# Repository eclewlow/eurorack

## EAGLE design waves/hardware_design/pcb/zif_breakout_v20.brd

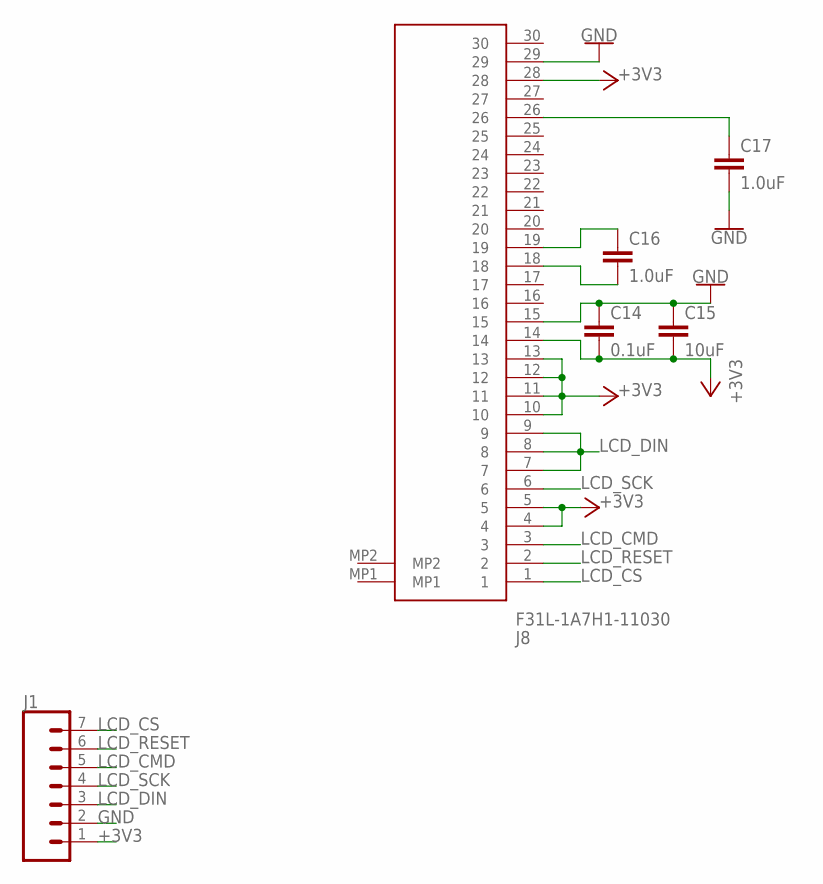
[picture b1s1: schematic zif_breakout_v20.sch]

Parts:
C14: 0.1uF; 0603
C15: 10uF; 0603
C16, C17: 1.0uF; 0603
J1: CONN_07; 1X07
J8: F31L-1A7H1-11030; F31L1A7H111030

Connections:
+3V3: C14.2, C15.2, J1.1, J8.4, J8.5, J8.10, J8.11, J8.12, J8.13, J8.14, J8.28
GND: C14.1, C15.1, C17.2, J1.2, J8.15, J8.29
LCD_CMD: J1.5, J8.3
LCD_CS: J1.7, J8.1
LCD_DIN: J1.3, J8.7, J8.8, J8.9
LCD_RESET: J1.6, J8.2
LCD_SCK: J1.4, J8.6
unnamed: C16.1, J8.19
unnamed: C17.1, J8.26
unnamed: C16.2, J8.18

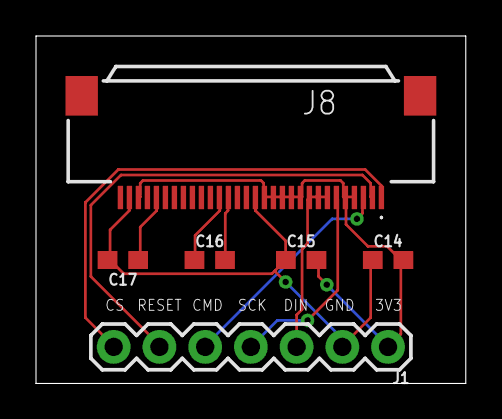
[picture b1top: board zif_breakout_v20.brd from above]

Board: 2 copper layers, 23.9 x 19.3 mm, 6 parts (0 on the bottom side), 10 nets.

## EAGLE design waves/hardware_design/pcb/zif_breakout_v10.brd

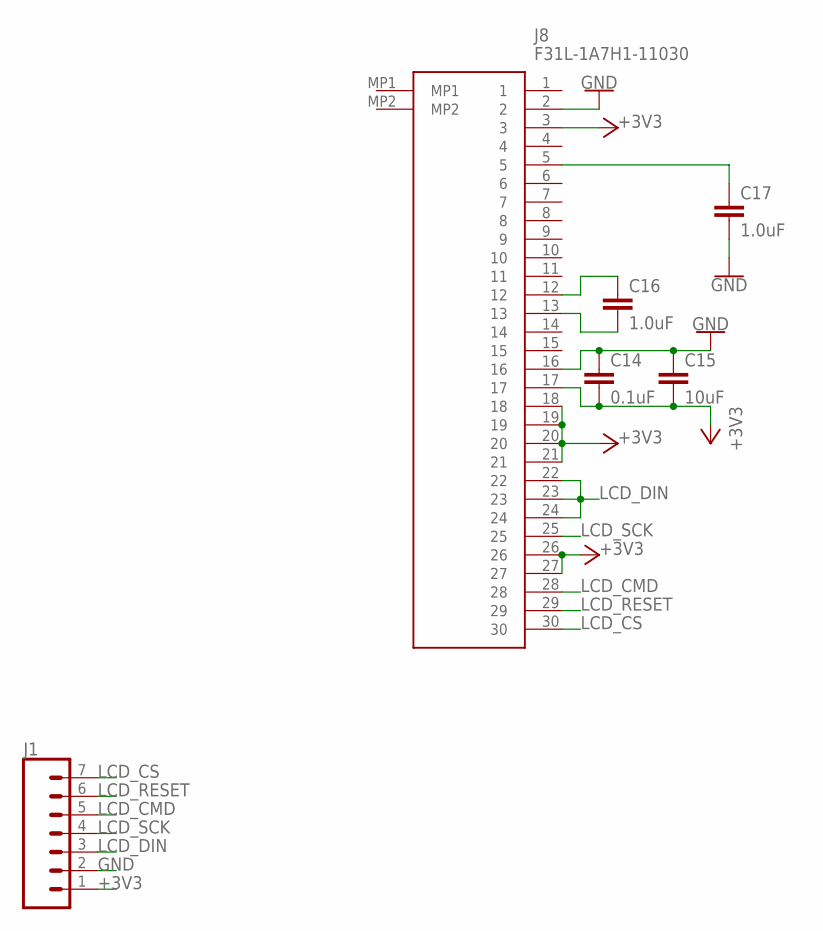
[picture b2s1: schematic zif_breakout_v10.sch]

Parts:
C14: 0.1uF; 0603
C15: 10uF; 0603
C16, C17: 1.0uF; 0603
J1: CONN_07; 1X07
J8: F31L-1A7H1-11030; F31L1A7H111030

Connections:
+3V3: C14.2, C15.2, J1.1, J8.3, J8.17, J8.18, J8.19, J8.20, J8.21, J8.26, J8.27
GND: C14.1, C15.1, C17.2, J1.2, J8.2, J8.16
LCD_CMD: J1.5, J8.28
LCD_CS: J1.7, J8.30
LCD_DIN: J1.3, J8.22, J8.23, J8.24
LCD_RESET: J1.6, J8.29
LCD_SCK: J1.4, J8.25
unnamed: C17.1, J8.5
unnamed: C16.2, J8.13
unnamed: C16.1, J8.12

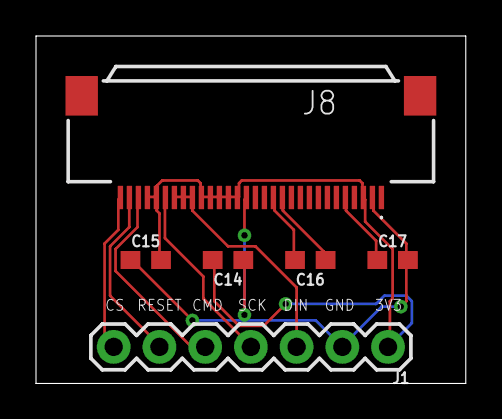
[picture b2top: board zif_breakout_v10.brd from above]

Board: 2 copper layers, 23.9 x 19.3 mm, 6 parts (0 on the bottom side), 10 nets.

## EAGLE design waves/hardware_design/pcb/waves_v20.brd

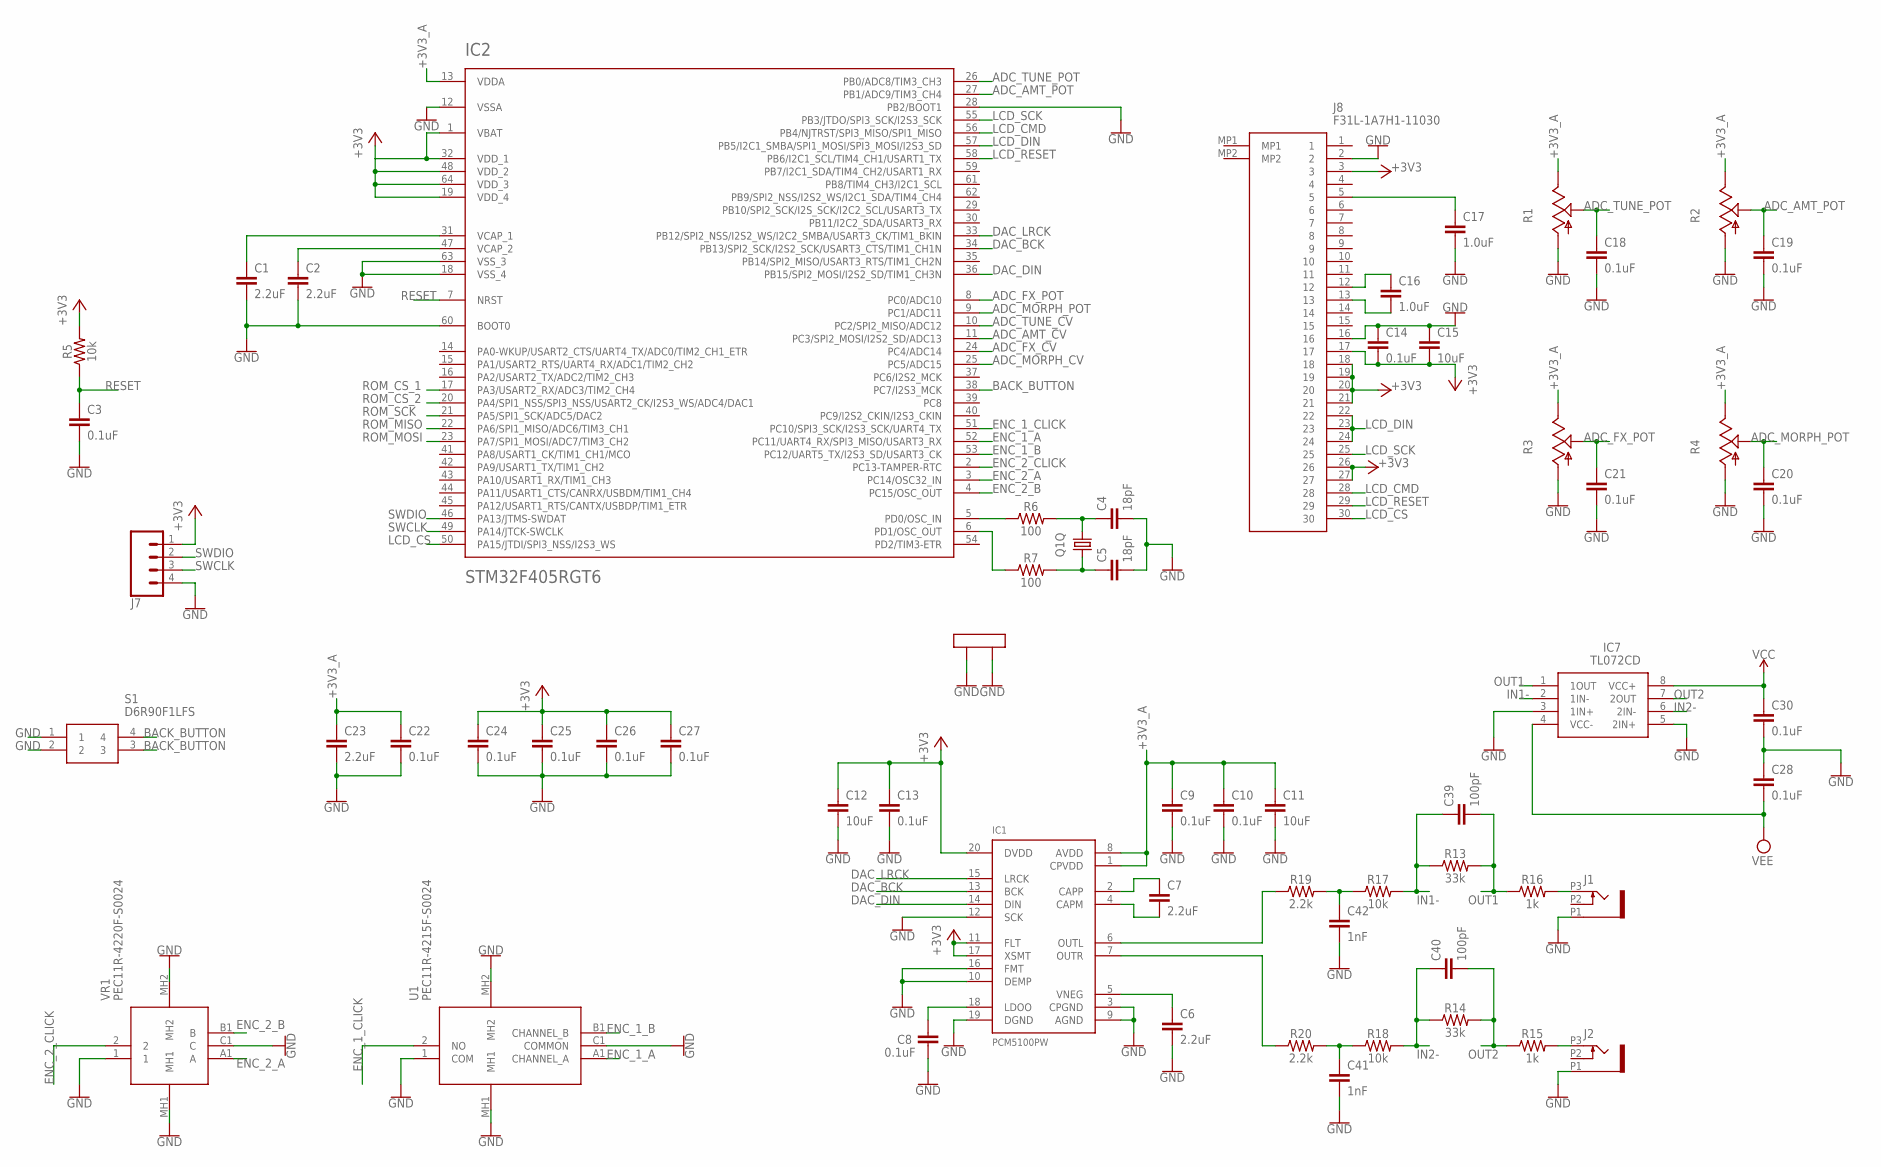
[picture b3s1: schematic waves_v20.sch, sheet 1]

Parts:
C1, C2, C6, C7, C23: 2.2uF; 0603
C3, C8, C9, C10, C13, C14, C18, C19, C20, C21, C22, C24, C25, C26, C27, C28, C30: 0.1uF; 0603
C4, C5: 18pF; 0603
C11, C12, C15: 10uF; 0603
C16, C17: 1.0uF; 0603
C39, C40: 100pF; 0603
C41, C42: 1nF; 0603
IC1: PCM5100PW; SSOP20
IC2: STM32F405RGT6; TQFP-10X10-64
IC7: TL072CD; SOIC127P600X175-8N
J1, J2: PJ301_THONKICONN6; WQP_PJ_301M6
J7: CONN_04; 1X04
J8: F31L-1A7H1-11030; F31L1A7H111030
Q1: CRYSTAL; CTS406
R1, R2, R3, R4: POT_USVERTICAL_PS; ALPS_POT_VERTICAL_PS
R5, R17, R18: 10k; 0603
R6, R7: 100; 0603
R13, R14: 33k; 0603
R15, R16: 1k; 0603
R19, R20: 2.2k; 0603
S1: D6R90F1LFS; D6C10F1LFS
U1: PEC11R-4215F-S0024; PEC11R4215FS0024
VR1: PEC11R-4220F-S0024; PEC11R4220FS0024

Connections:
+3V3: C12.1, C13.1, C14.2, C15.2, C24.1, C25.1, C26.1, C27.1, IC1.11 (FLT), IC1.17 (XSMT), IC1.20 (DVDD), IC2.1 (VBAT), IC2.19 (VDD_4), IC2.32 (VDD_1), IC2.48 (VDD_2), IC2.64 (VDD_3), J7.1, J8.3, J8.17, J8.18, J8.19, J8.20, J8.21, J8.26, J8.27, R5.2; also elsewhere on the board
+3V3_A: C9.1, C10.1, C11.1, C22.1, C23.1, IC1.1 (CPVDD), IC1.8 (AVDD), IC2.13 (VDDA), R1.P$1 (E), R2.P$1 (E), R3.P$1 (E), R4.P$1 (E); also elsewhere on the board
ADC_AMT_CV: IC2.11 (PC3/SPI2_MOSI/I2S2_SD/ADC13); also elsewhere on the board
ADC_AMT_POT: C19.1, IC2.27 (PB1/ADC9/TIM3_CH4), R2.P$2 (S)
ADC_FX_CV: IC2.24 (PC4/ADC14); also elsewhere on the board
ADC_FX_POT: C21.1, IC2.8 (PC0/ADC10), R3.P$2 (S)
ADC_MORPH_CV: IC2.25 (PC5/ADC15); also elsewhere on the board
ADC_MORPH_POT: C20.1, IC2.9 (PC1/ADC11), R4.P$2 (S)
ADC_TUNE_CV: IC2.10 (PC2/SPI2_MISO/ADC12); also elsewhere on the board
ADC_TUNE_POT: C18.1, IC2.26 (PB0/ADC8/TIM3_CH3), R1.P$2 (S)
BACK_BUTTON: IC2.38 (PC7/I2S3_MCK), S1.3, S1.4
DAC_BCK: IC1.13 (BCK), IC2.34 (PB13/SPI2_SCK/I2S2_SCK/USART3_CTS/TIM1_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)
DAC_DIN: IC1.14 (DIN), IC2.36 (PB15/SPI2_MOSI/I2S2_SD/TIM1_CH3N)
DAC_LRCK: IC1.15 (LRCK), IC2.33 (PB12/SPI2_NSS/I2S2_WS/I2C2_SMBA/USART3_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)
ENC_1_A: IC2.52 (PC11/UART4_RX/SPI3_MISO/USART3_RX), U1.A1 (CHANNEL_A)
ENC_1_B: IC2.53 (PC12/UART5_TX/I2S3_SD/USART3_CK), U1.B1 (CHANNEL_B)
ENC_1_CLICK: IC2.51 (PC10/SPI3_SCK/I2S3_SCK/UART4_TX), U1.2 (NO)
ENC_2_A: IC2.3 (PC14/OSC32_IN), VR1.A1 (A)
ENC_2_B: IC2.4 (PC15/OSC_OUT), VR1.B1 (B)
ENC_2_CLICK: IC2.2 (PC13-TAMPER-RTC), VR1.2
GND: C1.2, C2.2, C3.2, C4.2, C5.2, C6.2, C8.2, C9.2, C10.2, C11.2, C12.2, C13.2, C14.1, C15.1, C17.2, C18.2, C19.2, C20.2, C21.2, C22.2, C23.2, C24.2, C25.2, C26.2, C27.2, C28.1, C30.2, C41.2, C42.2, IC1.3 (CPGND), IC1.9 (AGND), IC1.10 (DEMP), IC1.12 (SCK), IC1.16 (FMT), IC1.19 (DGND), IC2.12 (VSSA), IC2.18 (VSS_4), IC2.28 (PB2/BOOT1), IC2.60 (BOOT0), IC2.63 (VSS_3), IC7.3 (1IN+), IC7.5 (2IN+), J1.P1 (1), J2.P1 (1), J7.4, J8.2, J8.16, Q1.2 (LID1), Q1.4 (LID2), R1.P$3 (A), R2.P$3 (A), R3.P$3 (A), R4.P$3 (A), S1.1, S1.2, U1.1 (COM), U1.C1 (COMMON), U1.MH1, U1.MH2, VR1.1, VR1.C1 (C), VR1.MH1, VR1.MH2; also elsewhere on the board
IN1-: C39.1, IC7.2 (1IN-), R13.1, R17.2
IN2-: C40.1, IC7.6 (2IN-), R14.1, R18.2
LCD_CMD: IC2.56 (PB4/NJTRST/SPI3_MISO/SPI1_MISO), J8.28
LCD_CS: IC2.50 (PA15/JTDI/SPI3_NSS/I2S3_WS), J8.30
LCD_DIN: IC2.57 (PB5/I2C1_SMBA/SPI1_MOSI/SPI3_MOSI/I2S3_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), J8.22, J8.23, J8.24
LCD_RESET: IC2.58 (PB6/I2C1_SCL/TIM4_CH1/USART1_TX), J8.29
LCD_SCK: IC2.55 (PB3/JTDO/SPI3_SCK/I2S3_SCK), J8.25
unnamed: C1.1, IC2.31 (VCAP_1)
unnamed: C2.1, IC2.47 (VCAP_2)
unnamed: C17.1, J8.5
unnamed: C6.1, IC1.5 (VNEG)
unnamed: C8.1, IC1.18 (LDOO)
unnamed: C7.1, IC1.2 (CAPP)
unnamed: C4.1, Q1.3 (2), R6.2
unnamed: IC2.6 (PD1/OSC_OUT), R7.1
unnamed: IC2.5 (PD0/OSC_IN), R6.1
unnamed: C5.1, Q1.1, R7.2
unnamed: C7.2, IC1.4 (CAPM)
unnamed: C16.2, J8.13
unnamed: C16.1, J8.12
unnamed: IC1.6 (OUTL), R19.1
unnamed: IC1.7 (OUTR), R20.1
unnamed: J2.P3 (3), R15.2
unnamed: J1.P3 (3), R16.2
unnamed: C42.1, R17.1, R19.2
unnamed: C41.1, R18.1, R20.2
OUT1: C39.2, IC7.1 (1OUT), R13.2, R16.1
OUT2: C40.2, IC7.7 (2OUT), R14.2, R15.1
RESET: C3.1, IC2.7 (NRST), R5.1
ROM_CS_1: IC2.17 (PA3/USART2_RX/ADC3/TIM2_CH4); also elsewhere on the board
ROM_CS_2: IC2.20 (PA4/SPI1_NSS/SPI3_NSS/USART2_CK/I2S3_WS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); also elsewhere on the board
ROM_MISO: IC2.22 (PA6/SPI1_MISO/ADC6/TIM3_CH1); also elsewhere on the board
ROM_MOSI: IC2.23 (PA7/SPI1_MOSI/ADC7/TIM3_CH2); also elsewhere on the board
ROM_SCK: IC2.21 (PA5/SPI1_SCK/ADC5/DAC2); also elsewhere on the board
SWCLK: IC2.49 (PA14/JTCK-SWCLK), J7.3
SWDIO: IC2.46 (PA13/JTMS-SWDAT), J7.2
VCC: C30.1, IC7.8 (VCC+); also elsewhere on the board
VEE: C28.2, IC7.4 (VCC-); also elsewhere on the board

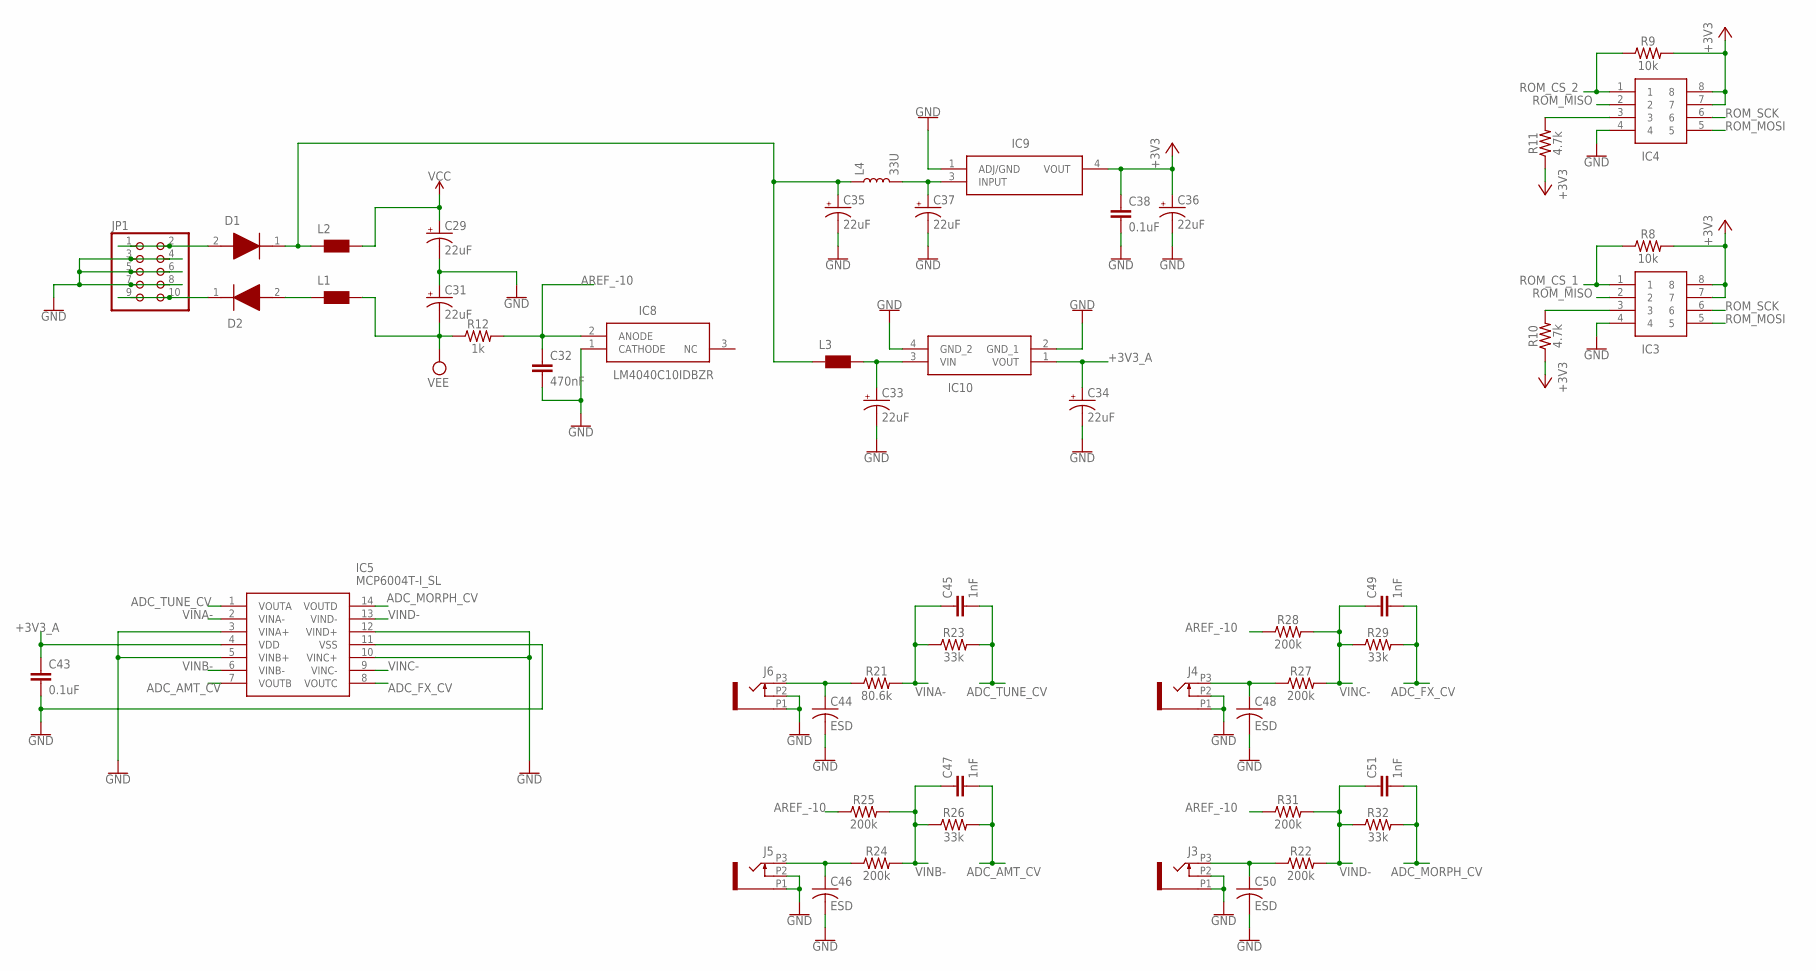
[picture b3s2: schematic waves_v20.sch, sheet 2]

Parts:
C29, C31, C33, C34, C35, C36, C37: 22uF; PANASONIC_C
C32: 470nF; 0402
C38, C43: 0.1uF; 0603
C44, C46, C48, C50: ESD; C0603
C45, C47, C49, C51: 1nF; 0603
D1, D2: 1N5819HW-7-F; SOD3716X145N
IC3, IC4: 1-2199298-2; DIPS762W70P254L1016H510Q8N
IC5: MCP6004T-I_SL; SOIC127P600X175-14N
IC8: LM4040C10IDBZR; SOT95P237X112-3N
IC9: LM1117DT-3.3_NOPB; TO228P991X238-3N
IC10: LD2981ABU33TR
J3, J4, J5, J6: PJ301_THONKICONN6; WQP_PJ_301M6
JP1: PINHD-2X5; 2X05
L1, L2, L3: WE-CBF_0603; 0603
L4: 33U; 0805
R8, R9: 10k; 0603
R10, R11: 4.7k; 0603
R12: 1k; 0603
R21: 80.6k; 0603
R22, R24, R25, R27, R28, R31: 200k; 0603
R23, R26, R29, R32: 33k; 0603

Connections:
+3V3: C36.+, C38.1, IC3.7, IC3.8, IC4.7, IC4.8, IC9.4 (VOUT), R8.2, R9.2, R10.1, R11.1; also elsewhere on the board
+3V3_A: C34.+, C43.1, IC5.4 (VDD), IC10.1 (VOUT); also elsewhere on the board
ADC_AMT_CV: C47.2, IC5.7 (VOUTB), R26.2; also elsewhere on the board
ADC_FX_CV: C49.2, IC5.8 (VOUTC), R29.2; also elsewhere on the board
ADC_MORPH_CV: C51.2, IC5.14 (VOUTD), R32.2; also elsewhere on the board
ADC_TUNE_CV: C45.2, IC5.1 (VOUTA), R23.2; also elsewhere on the board
AREF_-10: C32.1, IC8.2 (ANODE), R12.2, R25.1, R28.1, R31.1
GND: C29.-, C31.+, C32.2, C33.-, C34.-, C35.-, C36.-, C37.-, C38.2, C43.2, C44.2, C46.2, C48.2, C50.2, IC3.4, IC4.4, IC5.3 (VINA+), IC5.5 (VINB+), IC5.10 (VINC+), IC5.11 (VSS), IC5.12 (VIND+), IC8.1 (CATHODE), IC9.1 (ADJ/GND), IC10.2 (GND_1), IC10.4 (GND_2), J3.P1 (1), J3.P2 (2), J4.P1 (1), J4.P2 (2), J5.P1 (1), J5.P2 (2), J6.P1 (1), J6.P2 (2), JP1.3, JP1.4, JP1.5, JP1.6, JP1.7, JP1.8; also elsewhere on the board
unnamed: C46.1, J5.P3 (3), R24.1
unnamed: C44.1, J6.P3 (3), R21.1
unnamed: C48.1, J4.P3 (3), R27.1
unnamed: D2.1 (K), JP1.9, JP1.10
unnamed: IC3.3, R10.2
unnamed: D1.2 (A), JP1.1, JP1.2
unnamed: C35.+, D1.1 (K), L2.1, L3.1, L4.1
unnamed: C50.1, J3.P3 (3), R22.1
unnamed: D2.2 (A), L1.1
unnamed: C33.+, IC10.3 (VIN), L3.2
unnamed: IC4.3, R11.2
unnamed: C37.+, IC9.3 (INPUT), L4.2
ROM_CS_1: IC3.1, R8.1; also elsewhere on the board
ROM_CS_2: IC4.1, R9.1; also elsewhere on the board
ROM_MISO: IC3.2, IC4.2; also elsewhere on the board
ROM_MOSI: IC3.5, IC4.5; also elsewhere on the board
ROM_SCK: IC3.6, IC4.6; also elsewhere on the board
VCC: C29.+, L2.2; also elsewhere on the board
VEE: C31.-, L1.2, R12.1; also elsewhere on the board
VINA-: C45.1, IC5.2 (VINA-), R21.2, R23.1
VINB-: C47.1, IC5.6 (VINB-), R24.2, R25.2, R26.1
VINC-: C49.1, IC5.9 (VINC-), R27.2, R28.2, R29.1
VIND-: C51.1, IC5.13 (VIND-), R22.2, R31.2, R32.1

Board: 2 copper layers, 110 parts (96 on the bottom side), 76 nets, no tracks yet.

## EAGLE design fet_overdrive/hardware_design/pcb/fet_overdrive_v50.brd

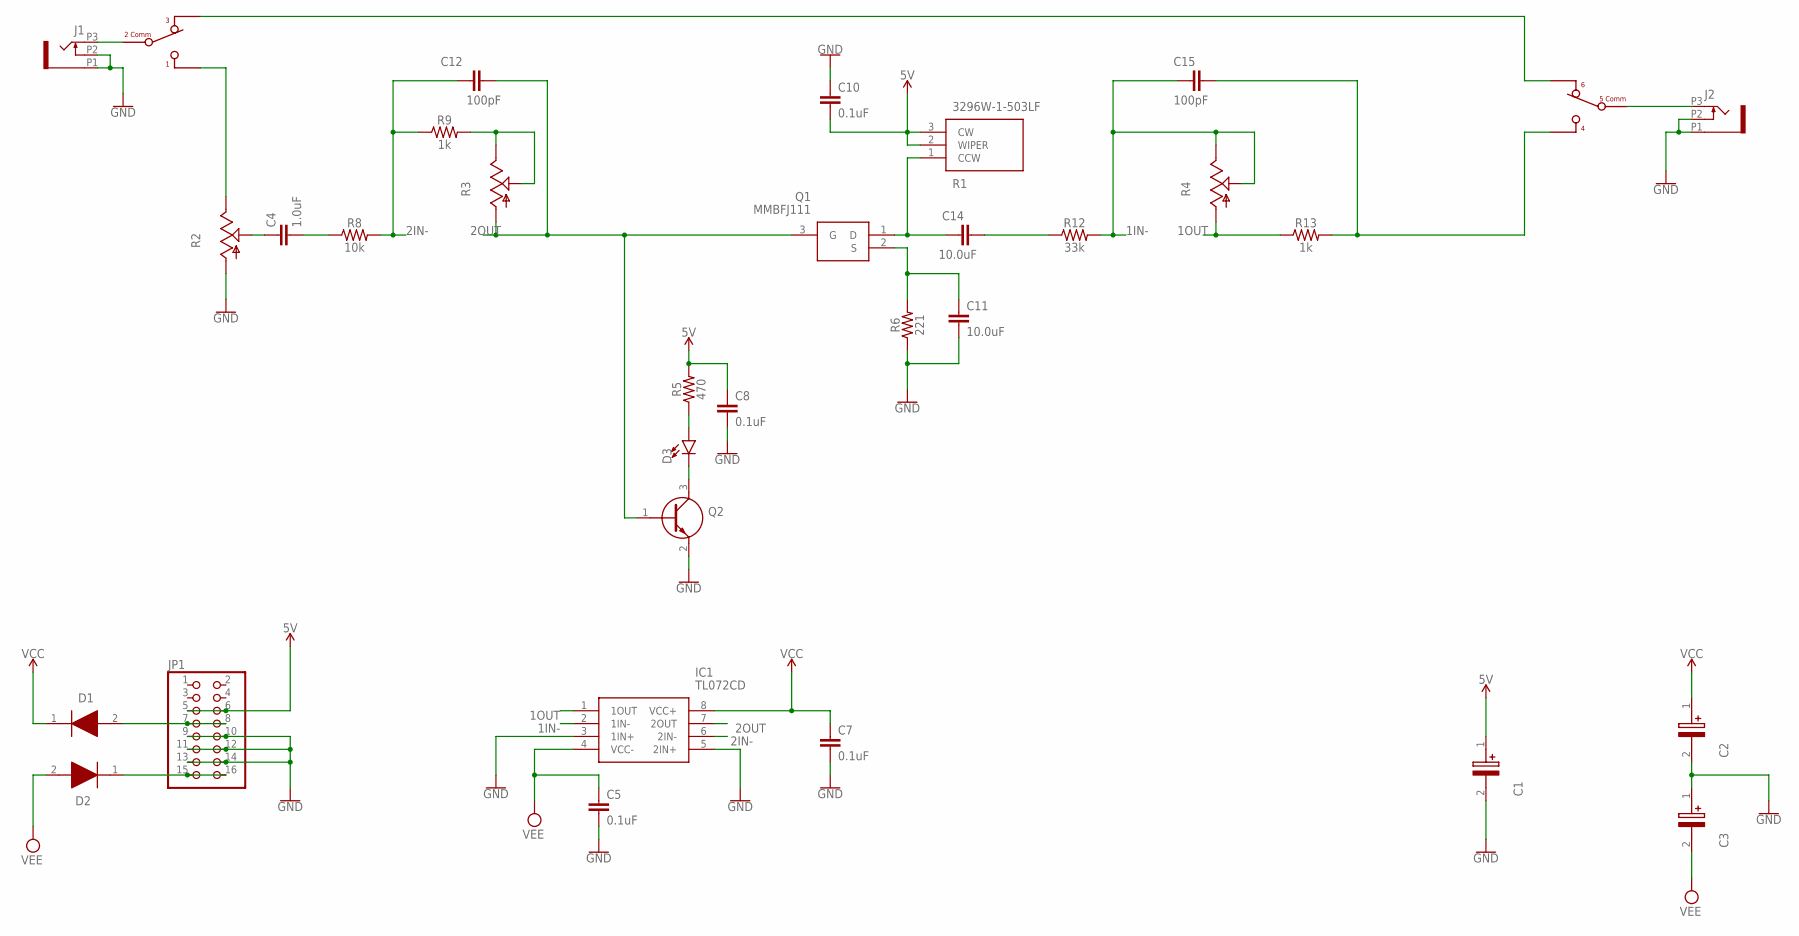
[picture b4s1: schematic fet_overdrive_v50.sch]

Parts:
C1: EEE-FP1E220AR; EEE0GA101SR
C2, C3: EEE-FK1V470P; EEE1AA101SP
C4: 1.0uF; 0603
C5, C7, C8, C10: 0.1uF; 0603
C11, C14: 10.0uF; 0603
C12, C15: 100pF; 0603
D1, D2: 1N5819HW-7-F; SOD3716X145N
D3: LED3MM; LED_3MM
IC1: TL072CD; SOIC127P600X175-8N
J1, J2: PJ301_THONKICONN6; WQP_PJ_301M6
JP1: PINHD-2X8; 2X08
Q1: MMBFJ111; SOT96P237X111-3N
Q2: SMMBT3904LT1G; SOT96P237X111-3N
R1: 3296W-1-503LF; 3296W-1
R2, R3, R4: POT_USVERTICAL_PS; ALPS_POT_VERTICAL_PS
R5: 470; 0603
R6: 221; 0603
R8: 10k; 0603
R9, R13: 1k; 0603
R12: 33k; 0603
U$2: DAILYWELL-DPDT

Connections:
1IN-: C15.1, IC1.2 (1IN-), R4.P$1 (E), R4.P$2 (S), R12.2
1OUT: IC1.1 (1OUT), R4.P$3 (A), R13.1
2IN-: C12.1, IC1.6 (2IN-), R8.2, R9.1
2OUT: C12.2, IC1.7 (2OUT), Q1.3 (G), Q2.1 (B), R3.P$3 (A)
5V: C1.1 (+), C8.1, C10.2, JP1.5, JP1.6, R1.2 (WIPER), R1.3 (CW), R5.2
GND: C1.2 (-), C2.2 (-), C3.1 (+), C5.2, C7.2, C8.2, C10.1, C11.2, IC1.3 (1IN+), IC1.5 (2IN+), J1.P1 (1), J1.P2 (2), J2.P1 (1), J2.P2 (2), JP1.9, JP1.10, JP1.11, JP1.12, JP1.13, JP1.14, Q2.2 (E), R2.P$3 (A), R6.1
unnamed: C15.2, R13.2, U$2.P$4
unnamed: J1.P3 (3), U$2.P$2
unnamed: D1.2 (A), JP1.7, JP1.8
unnamed: C4.1, R2.P$2 (S)
unnamed: C14.1, Q1.1 (D), R1.1 (CCW)
unnamed: R2.P$1 (E), U$2.P$1
unnamed: D3.A, R5.1
unnamed: D3.K (C), Q2.3 (C)
unnamed: C4.2, R8.1
unnamed: D2.1 (K), JP1.15, JP1.16
unnamed: C14.2, R12.1
unnamed: C11.1, Q1.2 (S), R6.2
unnamed: R3.P$1 (E), R3.P$2 (S), R9.2
unnamed: U$2.P$3, U$2.P$6
unnamed: J2.P3 (3), U$2.P$5
VCC: C2.1 (+), C7.1, D1.1 (K), IC1.8 (VCC+)
VEE: C3.2 (-), C5.1, D2.2 (A), IC1.4 (VCC-)

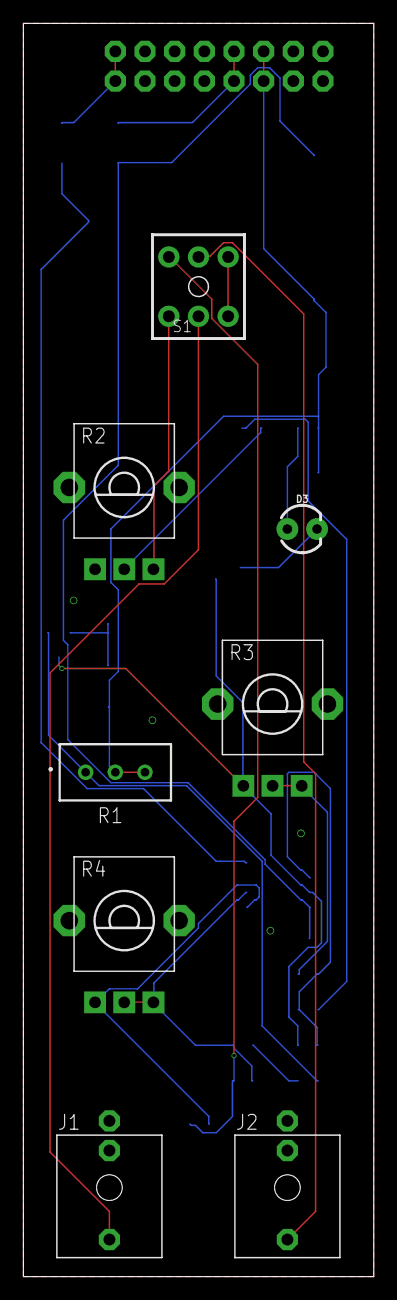
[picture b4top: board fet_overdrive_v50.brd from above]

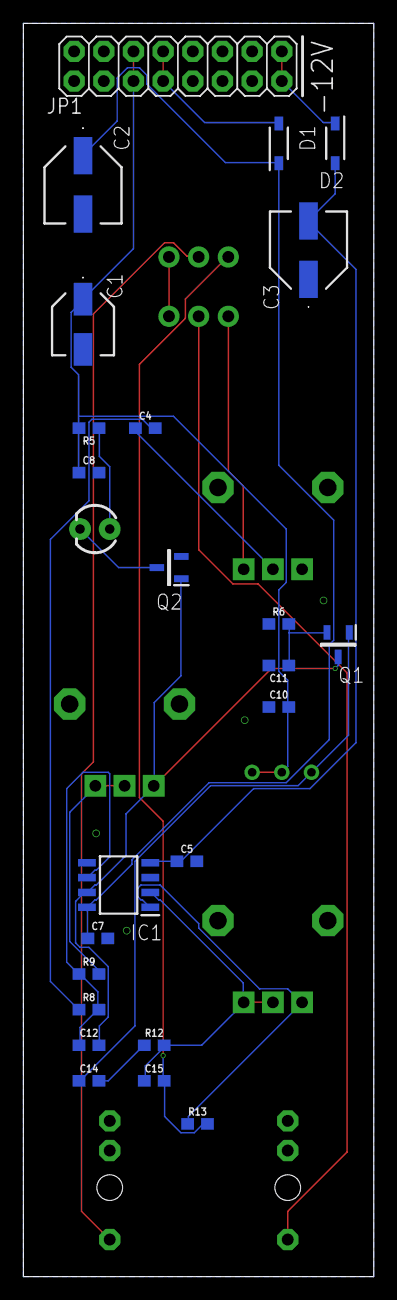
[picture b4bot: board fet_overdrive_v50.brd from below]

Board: 2 copper layers, 30.0 x 107.3 mm, 32 parts (24 on the bottom side), 23 nets.

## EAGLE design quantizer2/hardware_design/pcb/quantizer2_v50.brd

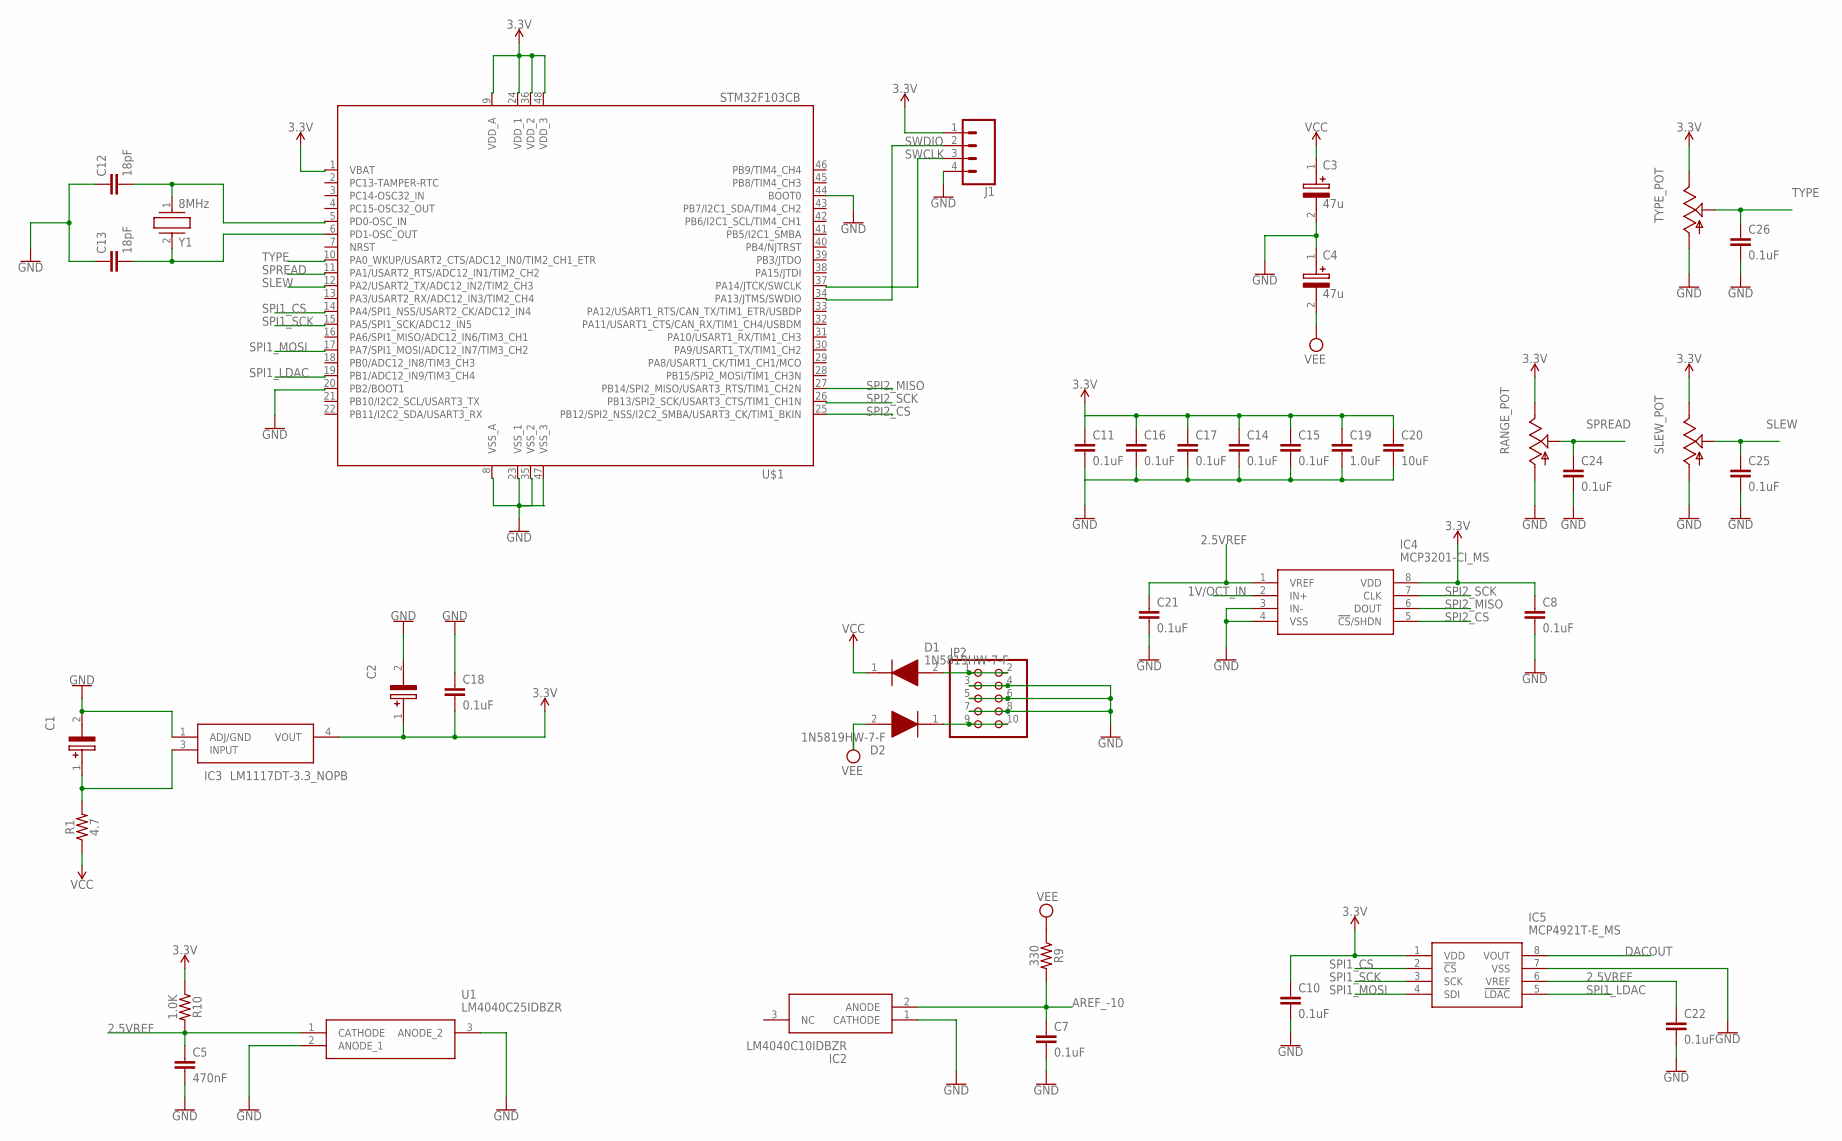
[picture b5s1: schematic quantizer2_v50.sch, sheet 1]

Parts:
C1, C2: 22uF; EEE0GA101SR
C3, C4: 47u; EEE1AA101SP
C5: 470nF; 0603
C7, C8, C10, C11, C14, C15, C16, C17, C18, C21, C22, C24, C25, C26: 0.1uF; 0603
C12, C13: 18pF; 0603
C19: 1.0uF; 0603
C20: 10uF; 0603
D1, D2: 1N5819HW-7-F; SOD3716X145N
IC2: LM4040C10IDBZR; SOT95P237X112-3N
IC3: LM1117DT-3.3_NOPB; TO228P991X238-3N
IC4: MCP3201-CI_MS; SOP65P490X110-8N
IC5: MCP4921T-E_MS; SOP65P490X110-8N
J1: CONN_04; 1X04
JP2: PINHD-2X5; 2X05
R1: 4.7; 1206
R9: 330; 0603
R10: 1.0K; 0603
RANGE_POT: POT_USVERTICAL_PS; ALPS_POT_VERTICAL_PS
SLEW_POT: POTENTIOMETER-ALPHA-9MM_VERTICAL_; POTENTIOMETER-ALPHA-9MM_VERTICAL
TYPE_POT: POT_USVERTICAL_PS; ALPS_POT_VERTICAL_PS
U1: LM4040C25IDBZR; SOT95P237X112-3N
U$1: STM32F103CB; LQFP48
Y1: 8MHz; ABLS

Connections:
1V/OCT_IN: IC4.2 (IN+); also elsewhere on the board
2.5VREF: C5.1, C21.1, C22.1, IC4.1 (VREF), IC5.6 (VREF), R10.2, U1.1 (CATHODE)
3.3V: C2.1 (+), C8.1, C10.1, C11.1, C14.1, C15.1, C16.1, C17.1, C18.2, C19.1, C20.1, IC3.4 (VOUT), IC4.8 (VDD), IC5.1 (VDD), J1.1, R10.1, RANGE_POT.P$1 (E), SLEW_POT.3 (E), TYPE_POT.P$1 (E), U$1.1 (VBAT), U$1.9 (VDD_A), U$1.24 (VDD_1), U$1.36 (VDD_2), U$1.48 (VDD_3)
AREF_-10: C7.1, IC2.2 (ANODE), R9.2; also elsewhere on the board
DACOUT: IC5.8 (VOUT); also elsewhere on the board
GND: C1.2 (-), C2.2 (-), C3.2 (-), C4.1 (+), C5.2, C7.2, C8.2, C10.2, C12.1, C13.1, C18.1, C21.2, C22.2, C24.2, C25.2, C26.2, IC2.1 (CATHODE), IC3.1 (ADJ/GND), IC4.3 (IN-), IC4.4 (VSS), IC5.7 (VSS), J1.4, JP2.3, JP2.4, JP2.5, JP2.6, JP2.7, JP2.8, RANGE_POT.P$3 (A), SLEW_POT.1 (A), TYPE_POT.P$3 (A), U1.2 (ANODE_1), U1.3 (ANODE_2), U$1.8 (VSS_A), U$1.20 (PB2/BOOT1), U$1.23 (VSS_1), U$1.35 (VSS_2), U$1.44 (BOOT0), U$1.47 (VSS_3); also elsewhere on the board
unnamed: C1.1 (+), IC3.3 (INPUT), R1.2
unnamed: D1.2 (A), JP2.1, JP2.2
unnamed: D2.1 (K), JP2.9, JP2.10
unnamed: C12.2, U$1.5 (PD0-OSC_IN), Y1.1
unnamed: C13.2, U$1.6 (PD1-OSC_OUT), Y1.2
unnamed: C11.2, C14.2, C15.2, C16.2, C17.2, C19.2, C20.2
SLEW: C25.1, SLEW_POT.2 (S), U$1.12 (PA2/USART2_TX/ADC12_IN2/TIM2_CH3)
SPI1_CS: IC5.2 (!CS), U$1.14 (PA4/SPI1_NSS/USART2_CK/ADC12_IN4)
SPI1_LDAC: IC5.5 (!LDAC), U$1.19 (PB1/ADC12_IN9/TIM3_CH4)
SPI1_MOSI: IC5.4 (SDI), U$1.17 (PA7/SPI1_MOSI/ADC12_IN7/TIM3_CH2)
SPI1_SCK: IC5.3 (SCK), U$1.15 (PA5/SPI1_SCK/ADC12_IN5)
SPI2_CS: IC4.5 (!CS!/SHDN), U$1.25 (PB12/SPI2_NSS/I2C2_SMBA/USART3_CK/TIM1_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)
SPI2_MISO: IC4.6 (DOUT), U$1.27 (PB14/SPI2_MISO/USART3_RTS/TIM1_CH2N)
SPI2_SCK: IC4.7 (CLK), U$1.26 (PB13/SPI2_SCK/USART3_CTS/TIM1_CH1N)
SPREAD: C24.1, RANGE_POT.P$2 (S), U$1.11 (PA1/USART2_RTS/ADC12_IN1/TIM2_CH2)
SWCLK: J1.3, U$1.37 (PA14/JTCK/SWCLK)
SWDIO: J1.2, U$1.34 (PA13/JTMS/SWDIO)
TYPE: C26.1, TYPE_POT.P$2 (S), U$1.10 (PA0_WKUP/USART2_CTS/ADC12_IN0/TIM2_CH1_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)
VCC: C3.1 (+), D1.1 (K), R1.1; also elsewhere on the board
VEE: C4.2 (-), D2.2 (A), R9.1; also elsewhere on the board

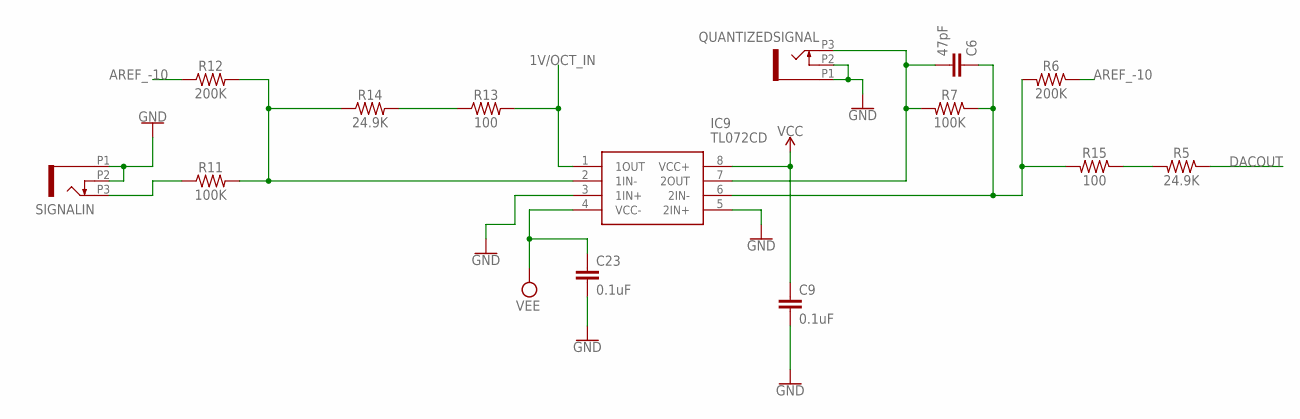
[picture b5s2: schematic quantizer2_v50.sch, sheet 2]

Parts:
C6: 47pF; 0603
C9, C23: 0.1uF; 0603
IC9: TL072CD; SOIC127P600X175-8N
QUANTIZEDSIGNAL: PJ301_THONKICONN6; WQP_PJ_301M6
R5, R14: 24.9K; 0603
R6, R12: 200K; 0603
R7, R11: 100K; 0603
R13, R15: 100; 0603
SIGNALIN: PJ301_THONKICONN6; WQP_PJ_301M6

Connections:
1V/OCT_IN: IC9.1 (1OUT), R13.2; also elsewhere on the board
AREF_-10: R6.1, R12.1; also elsewhere on the board
DACOUT: R5.1; also elsewhere on the board
GND: C9.2, C23.2, IC9.3 (1IN+), IC9.5 (2IN+), QUANTIZEDSIGNAL.P1 (1), QUANTIZEDSIGNAL.P2 (2), SIGNALIN.P1 (1), SIGNALIN.P2 (2); also elsewhere on the board
unnamed: R11.1, SIGNALIN.P3 (3)
unnamed: IC9.2 (1IN-), R11.2, R12.2, R14.1
unnamed: C6.2, IC9.7 (2OUT), QUANTIZEDSIGNAL.P3 (3), R7.2
unnamed: R13.1, R14.2
unnamed: R5.2, R15.1
unnamed: C6.1, IC9.6 (2IN-), R6.2, R7.1, R15.2
VCC: C9.1, IC9.8 (VCC+); also elsewhere on the board
VEE: C23.1, IC9.4 (VCC-); also elsewhere on the board

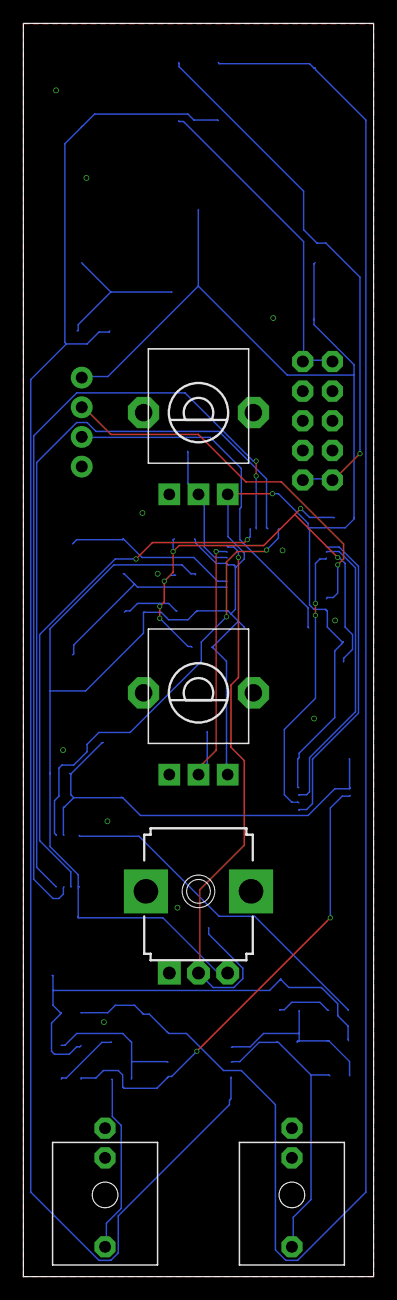
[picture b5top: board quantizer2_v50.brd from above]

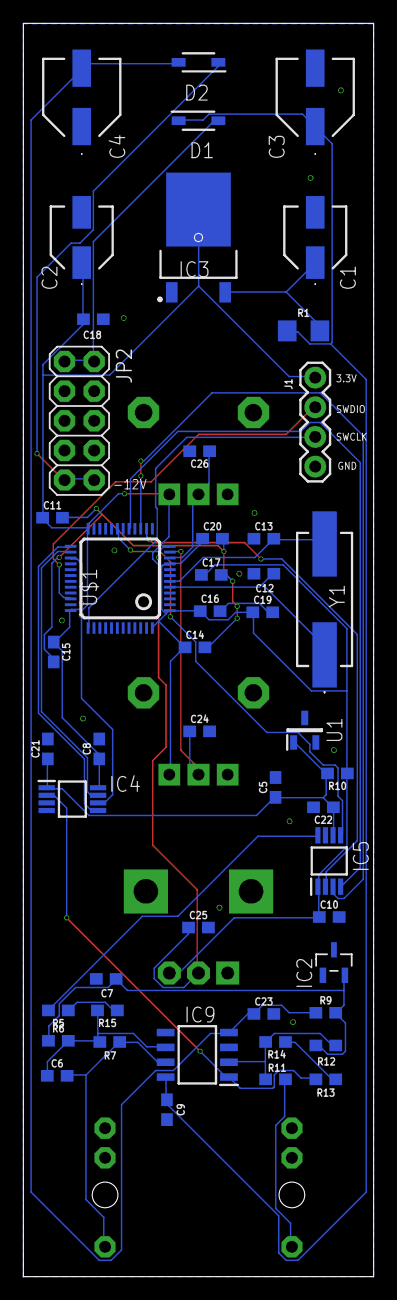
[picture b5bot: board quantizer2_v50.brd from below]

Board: 2 copper layers, 30.0 x 107.3 mm, 54 parts (49 on the bottom side), 32 nets.

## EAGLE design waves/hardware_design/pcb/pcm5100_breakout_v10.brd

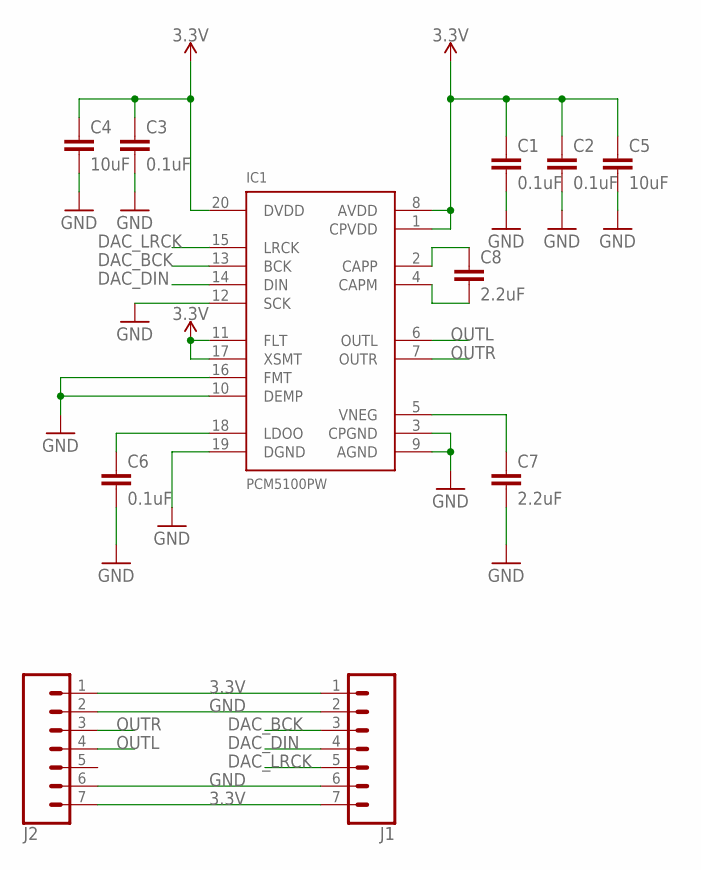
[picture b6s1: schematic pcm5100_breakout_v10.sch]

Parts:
C1, C2, C3, C6: 0.1uF; 0603
C4, C5: 10uF; 0603
C7, C8: 2.2uF; 0603
IC1: PCM5100PW; SSOP20
J1, J2: CONN_07; 1X07

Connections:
3.3V: C1.1, C2.1, C3.1, C4.1, C5.1, IC1.1 (CPVDD), IC1.8 (AVDD), IC1.11 (FLT), IC1.17 (XSMT), IC1.20 (DVDD), J1.1, J1.7, J2.1, J2.7
DAC_BCK: IC1.13 (BCK), J1.3
DAC_DIN: IC1.14 (DIN), J1.4
DAC_LRCK: IC1.15 (LRCK), J1.5
GND: C1.2, C2.2, C3.2, C4.2, C5.2, C6.2, C7.2, IC1.3 (CPGND), IC1.9 (AGND), IC1.10 (DEMP), IC1.12 (SCK), IC1.16 (FMT), IC1.19 (DGND), J1.2, J1.6, J2.2, J2.6
unnamed: C6.1, IC1.18 (LDOO)
unnamed: C7.1, IC1.5 (VNEG)
unnamed: C8.2, IC1.4 (CAPM)
unnamed: C8.1, IC1.2 (CAPP)
OUTL: IC1.6 (OUTL), J2.4
OUTR: IC1.7 (OUTR), J2.3

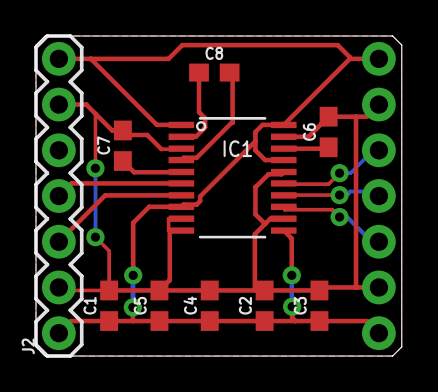
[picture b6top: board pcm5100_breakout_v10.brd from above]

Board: 2 copper layers, 20.3 x 17.8 mm, 11 parts (1 on the bottom side), 11 nets.

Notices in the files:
parts and their libraries:
SparkFun-Capacitors: Licensing: Creative Commons ShareAlike 4.0 International - https://creativecommons.org/licenses/by-sa/4.0
